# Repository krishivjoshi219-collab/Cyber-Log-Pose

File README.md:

# 🏴‍☠️ Cyber Log Pose

YO HACK CLUB REVIEWERS !!!!!!!!!!

this is **Cyber Log Pose**, my tiny pocket IR hacker fob thingy for Half-Life Week 5 freestyle. i was first trying to do a whole smartwatch and then my brain basically melted so i scoped it down into something i can ACTUALLY build in build week without crying lol.

it is like a little straw-hat themed remote cloner / IR blaster with an OLED and a 5-way nav button. basically point it at a TV / projector / random remote and later it can replay commands. the firmware right now is barebones because this week was mostly design week, but the pcb + case + bom are ready.

---

## screenshots from my devlog

schematic / pcb / cad chaos from the Half-Life journal:

---

## what it does

- uses an **ESP32-C3 SuperMini** as the brain
- has a **0.96 inch I2C OLED** for menus
- has an **IR transmitter** for blasting remote commands
- has a **VS1838B IR receiver** for learning / reading remote signals
- has a **5-way navigation button** so it feels like a tiny gadget not a random breadboard mess
- runs from a **420mAh LiPo** with a **TP4056 Type-C charger**
- has a custom pcb with straw-hat-ish silkscreen because plain rectangles are BORING
- has a 2-piece 3d printed case, and i even added a charger U-cutout so the usb cable can actually go inside

---

## repo map

```txt
├── BOM.csv                 <- parts + prices, kept around $32-$33 with print reserve
├── JOURNAL.md              <- synced Half-Life devlog with my screenshots
├── PCB/
│   ├── Cyber Log Pose.kicad_pro
│   ├── Cyber Log Pose.kicad_sch
│   ├── Cyber Log Pose.kicad_pcb
│   └── Cyber Log Pose.step
├── CAD/
│   ├── Cyber Log Pose - Base - Charger U Cutout.stl
│   └── Cyber Log Pose - Top.stl
├── firmware/
│   ├── main.py
│   └── README.md
└── production/             <- gerbers will go here when i export final fab files
```

---

## pinout

| thing | GPIO |
| --- | --- |
| OLED SDA | GPIO0 |
| OLED SCL | GPIO5 |
| IR TX | GPIO1 |
| IR RX | GPIO7 |
| Battery sense | GPIO2 |
| Nav up | GPIO4 |
| Nav down | GPIO3 |
| Nav left | GPIO6 |
| Nav right | GPIO10 |
| Nav press | GPIO20 |

important: **ESP32-C3 GPIO is 3.3V ONLY**. no 5v signal jumpscare pls.

---

## budget

latest BOM is around:

```txt
₹2869 / about $32.63
```

that includes pcb at ₹949 and 3d print reserve for around 15g print weight. it is TIGHT but still under my $33 target.

---

## current status

- schematic done
- pcb routed
- DRC = 0 errors
- case STL exported
- charger cutout added to base
- barebones firmware added
- build week me still has to write the real IR decode/replay firmware

---

## why i made it

because i wanted something with the hacker energy of my crazy smartwatch idea but actually buildable in time. this is still cool, still useful, and doesn't need 100 tiny smartwatch parts. also it is One Piece themed because obviously.

ok bye reviewers pls approve this tiny chaos machine :D

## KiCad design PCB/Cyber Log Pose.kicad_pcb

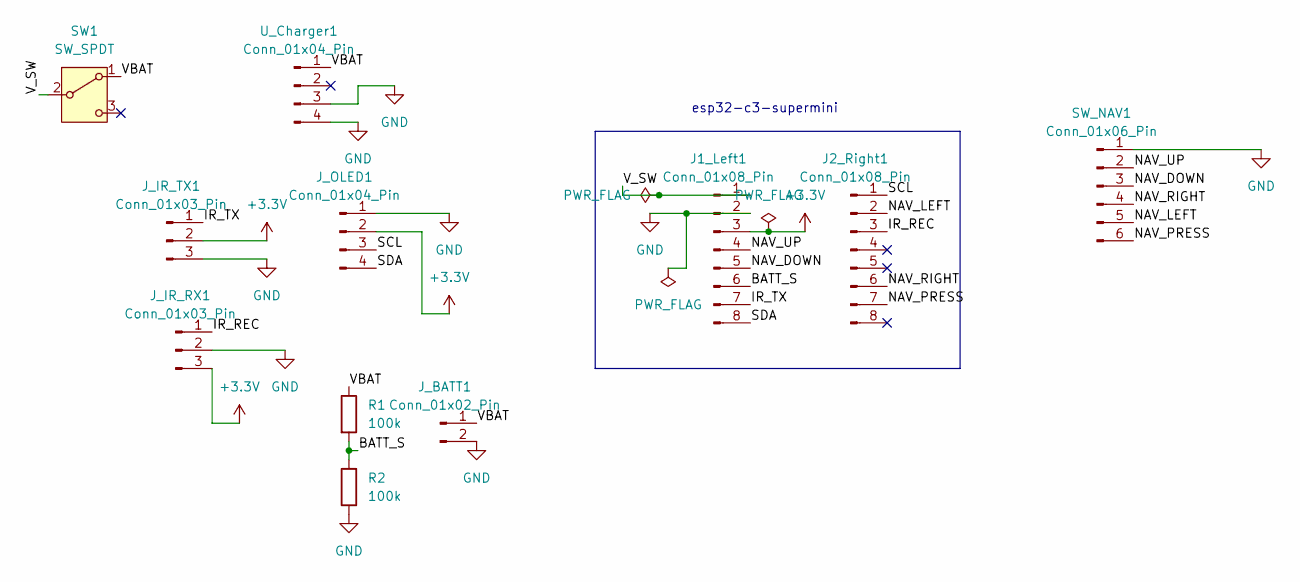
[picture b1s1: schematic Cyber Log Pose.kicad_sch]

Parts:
J1_Left1, J2_Right1: Conn_01x08_Pin; PinHeader_1x08_P2.54mm_Vertical
J_BATT1: Conn_01x02_Pin; PinSocket_1x02_P2.54mm_Vertical
J_IR_RX1: Conn_01x03_Pin; PinSocket_1x03_P2.54mm_Vertical
J_IR_TX1: Conn_01x03_Pin; PinSocket_1x03_P2.54mm_Vertical
J_OLED1: Conn_01x04_Pin; PinSocket_1x04_P2.54mm_Vertical
R1, R2: 100k; R_0805_2012Metric
SW1: SW_SPDT; PinSocket_1x03_P2.54mm_Vertical
SW_NAV1: Conn_01x06_Pin; PinSocket_1x06_P2.54mm_Vertical
U_Charger1: Conn_01x04_Pin; PinSocket_1x04_P2.54mm_Vertical

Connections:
+3.3V: J1_Left1.3, J_IR_RX1.3, J_IR_TX1.2, J_OLED1.2
/BATT_S: J1_Left1.6, R1.2, R2.2
/IR_REC: J2_Right1.3, J_IR_RX1.1
/IR_TX: J1_Left1.7, J_IR_TX1.1
/NAV_DOWN: J1_Left1.5, SW_NAV1.3
/NAV_LEFT: J2_Right1.2, SW_NAV1.5
/NAV_PRESS: J2_Right1.7, SW_NAV1.6
/NAV_RIGHT: J2_Right1.6, SW_NAV1.4
/NAV_UP: J1_Left1.4, SW_NAV1.2
/SCL: J2_Right1.1, J_OLED1.3
/SDA: J1_Left1.8, J_OLED1.4
/VBAT: J_BATT1.1, R1.1, SW1.1 (A), U_Charger1.1
/V_SW: J1_Left1.1, SW1.2 (B)
GND: J1_Left1.2, J_BATT1.2, J_IR_RX1.2, J_IR_TX1.3, J_OLED1.1, R2.1, SW_NAV1.1, U_Charger1.3, U_Charger1.4

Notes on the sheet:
esp32-c3-supermini

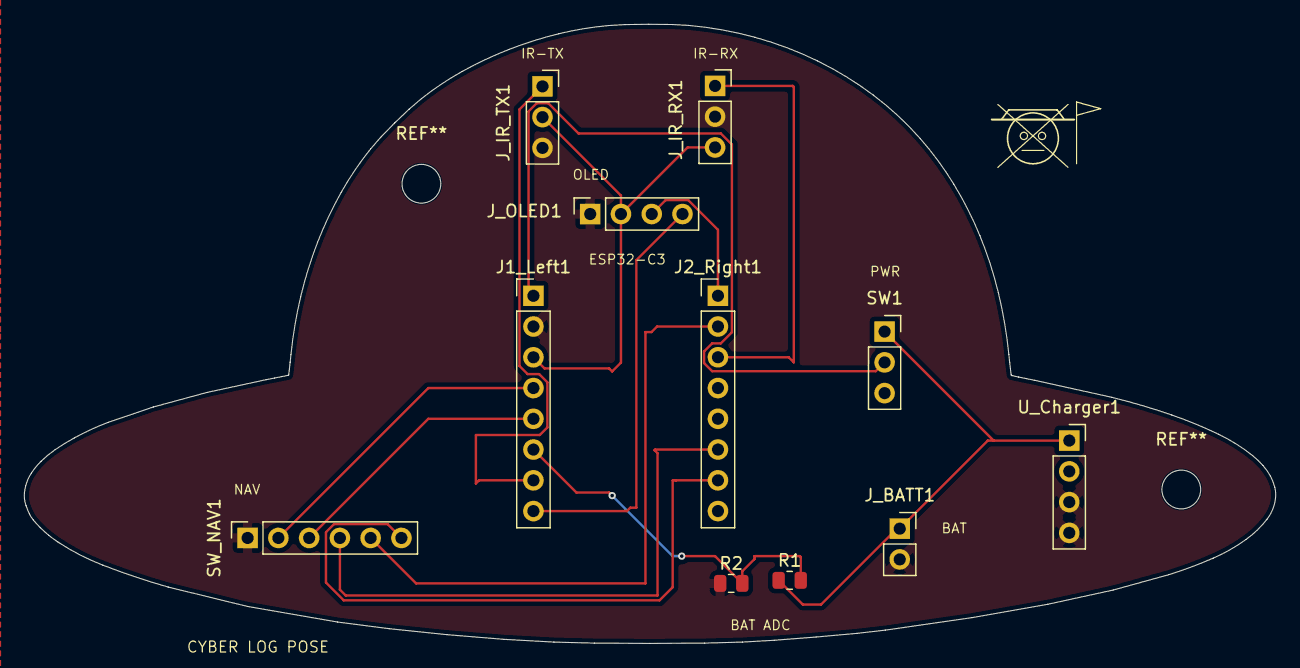
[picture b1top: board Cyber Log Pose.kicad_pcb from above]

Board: 2 copper layers, 103.3 x 51.1 mm, 11 parts (0 on the bottom side), 14 nets.

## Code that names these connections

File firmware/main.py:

# Cyber Log Pose - barebones MicroPython firmware
# ESP32-C3 SuperMini + SSD1306 OLED + IR tx/rx + 5-way nav
# this is just the starter build week firmware, not the final boss code yet lol

from machine import Pin, I2C, ADC
import time

# ===== pin map from the PCB =====
PIN_NAV_UP = 4
PIN_NAV_DOWN = 3
PIN_BATT = 2
PIN_IR_TX = 1
PIN_SDA = 0
PIN_SCL = 5
PIN_NAV_LEFT = 6
PIN_IR_RX = 7
PIN_NAV_RIGHT = 10
PIN_NAV_PRESS = 20

# ===== setup =====
nav_up = Pin(PIN_NAV_UP, Pin.IN, Pin.PULL_UP)
nav_down = Pin(PIN_NAV_DOWN, Pin.IN, Pin.PULL_UP)
nav_left = Pin(PIN_NAV_LEFT, Pin.IN, Pin.PULL_UP)
nav_right = Pin(PIN_NAV_RIGHT, Pin.IN, Pin.PULL_UP)
nav_press = Pin(PIN_NAV_PRESS, Pin.IN, Pin.PULL_UP)

ir_tx = Pin(PIN_IR_TX, Pin.OUT)
ir_rx = Pin(PIN_IR_RX, Pin.IN)

battery = ADC(Pin(PIN_BATT))
battery.atten(ADC.ATTN_11DB)

i2c = I2C(0, scl=Pin(PIN_SCL), sda=Pin(PIN_SDA), freq=400000)

# OLED is optional at boot so firmware does not just die if wiring is wrong
try:
    import ssd1306
    oled = ssd1306.SSD1306_I2C(128, 64, i2c)
except Exception as e:
    oled = None
    print("OLED not ready:", e)

menu = ["IR BLAST", "IR READ", "BATTERY", "ABOUT"]
index = 0


def pressed(pin):
    return pin.value() == 0


def battery_voltage():
    # divider is 100k/100k so ADC pin sees half the battery voltage
    raw = battery.read()
    # rough estimate for ESP32 ADC range with 11dB, good enough for first firmware
    v_adc = (raw / 4095) * 3.3
    return v_adc * 2


def draw():
    if oled is None:
        return
    oled.fill(0)
    oled.text("CYBER LOG POSE", 3, 0)
    oled.text("-" * 16, 0, 10)
    for i, item in enumerate(menu):
        prefix = ">" if i == index else " "
        oled.text(prefix + item, 0, 20 + i * 10)
    oled.show()


def blast_test():
    # simple visible debug burst, not real NEC yet
    # real IR remote codes come in build week
    for _ in range(80):
        ir_tx.value(1)
        time.sleep_us(13)
        ir_tx.value(0)
        time.sleep_us(13)


def show_battery():
    v = battery_voltage()
    if oled:
        oled.fill(0)
        oled.text("BATTERY", 0, 0)
        oled.text("%.2f V" % v, 0, 18)
        oled.text("press to back", 0, 45)
        oled.show()
    print("battery", v)


def show_about():
    if oled:
        oled.fill(0)
        oled.text("Cyber Log Pose", 0, 0)
        oled.text("IR fob thingy", 0, 14)
        oled.text("week 5 !!!", 0, 28)
        oled.text("press to back", 0, 50)
        oled.show()


draw()
last = time.ticks_ms()

while True:
    if time.ticks_diff(time.ticks_ms(), last) > 160:
        if pressed(nav_up):
            index = (index - 1) % len(menu)
            draw()
            last = time.ticks_ms()
        elif pressed(nav_down):
            index = (index + 1) % len(menu)
            draw()
            last = time.ticks_ms()
        elif pressed(nav_press):
            selected = menu[index]
            if selected == "IR BLAST":
                blast_test()
            elif selected == "BATTERY":
                show_battery()
            elif selected == "ABOUT":
                show_about()
            else:
                print("IR RX state:", ir_rx.value())
            last = time.ticks_ms()

    time.sleep_ms(10)
